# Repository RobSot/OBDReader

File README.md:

# OBDReader
OBD to USB interface development

The purpose of this development is to bring an open source OBD-USB interface to the comunity. Whith it you can develop your own applications above it. 
It has CAN connectivity via the OBD port and USB serial conectivity via the USB port.

*** The source code is organized like this:

1.- The folder src/Hardware_Source_code/ contains two folders. Both are MplabX 2.26 projects, one of them is the firmware and the other is the utility car emulator.
2.- The folder src/Software_Source_code/ contains one folder. This is the Qt creator 5 project and is the GUI application.
3.- In the src/ folder exist an .hex file containing the latest version of the OBDReader firmware ready to flash on the device.

Hope you enjoy it!!

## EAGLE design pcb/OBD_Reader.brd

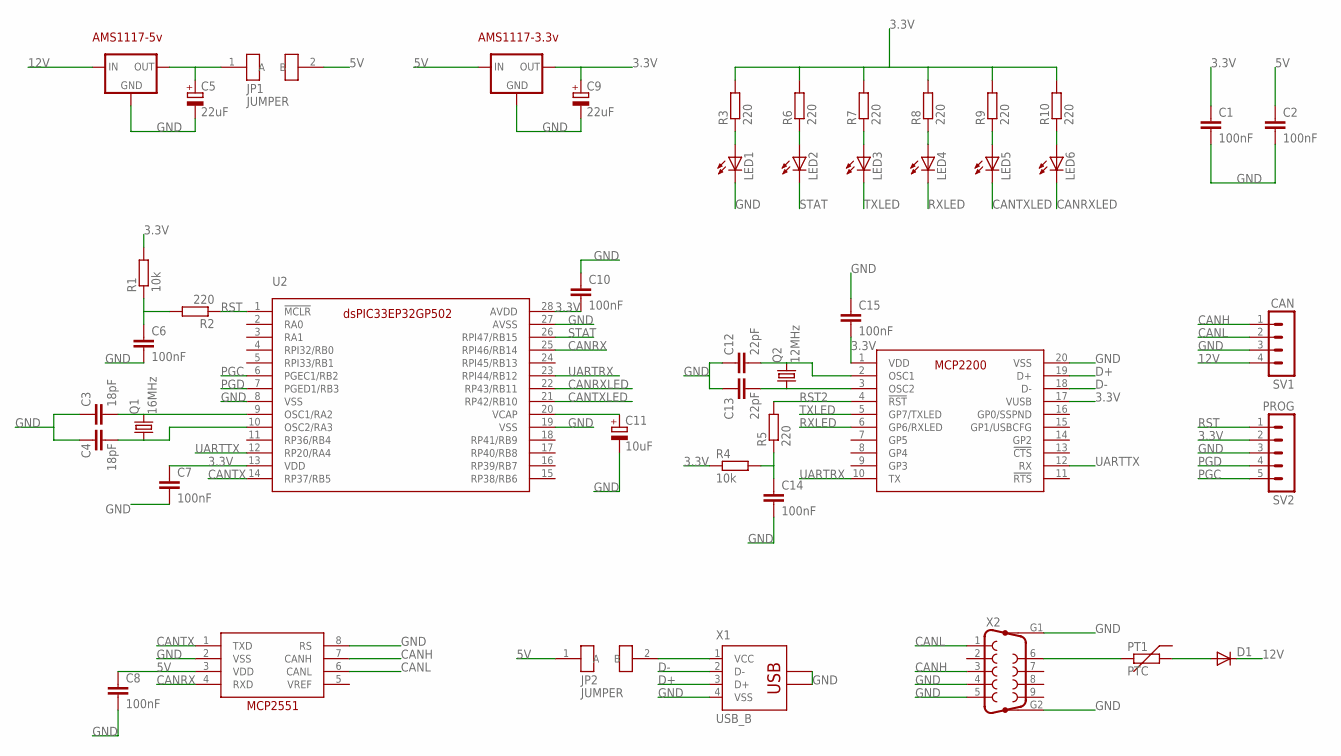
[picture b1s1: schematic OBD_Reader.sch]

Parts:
C1, C2, C6, C7, C8, C10, C14, C15: 100nF; C0603
C3, C4: 18pF; C0603
C5, C9: 22uF; CT3216
C11: 10uF; CT3216
C12, C13: 22pF; C0603
D1: DIODE-SMB; SMB
JP1, JP2: JUMPER; 1206
LED1, LED2, LED3, LED4, LED5, LED6: LEDCHIPLED_0603; CHIPLED_0603
PT1: PTC; PTC_1206
Q1: 16MHz; HC49/S
Q2: 12MHz; HC49/S
R1, R4: 10k; R0603
R2, R3, R5, R6, R7, R8, R9, R10: 220; R0603
SV1: CAN; MA04-1
SV2: PROG; MA05-1
U1: AMS1117_5V; SOT-223
U2: DSPIC33EP32GP502; SSOP28
U3: MCP2551; SOIC20
U4: AMS1117_3.3V; SOT-223
U5: MCP2200; SSOP20
X1: USB_B; 85-32004-00X
X2: F09HP

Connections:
3.3V: C1.1, C7.1, C9.+, C10.2, C15.2, R1.2, R3.2, R4.1, R6.2, R7.2, R8.2, R9.2, R10.2, SV2.2, U2.13 (VDD), U2.28 (AVDD), U4.2 (OUT), U5.1 (VDD), U5.17 (VUSB)
5V: C2.1, C8.1, JP1.2 (B), JP2.1 (A), U3.3 (VDD), U4.3 (IN)
12V: D1.C, SV1.4, U1.3 (IN)
CANH: SV1.1, U3.7 (CANH), X2.3
CANL: SV1.2, U3.6 (CANL), X2.1
CANRX: U2.25 (RPI46/RB14), U3.4 (RXD)
CANRXLED: LED6.C, U2.22 (RP43/RB11)
CANTX: U2.14 (RP37/RB5), U3.1 (TXD)
CANTXLED: LED5.C, U2.21 (RP42/RB10)
D+: U5.19 (D+), X1.3 (D+)
D-: U5.18 (D-), X1.2 (D-)
GND: C1.2, C2.2, C3.1, C4.1, C5.-, C6.2, C7.2, C8.2, C9.-, C10.1, C11.-, C12.1, C13.1, C14.2, C15.1, LED1.C, SV1.3, SV2.3, U1.1 (GND), U2.8 (VSS), U2.19 (VSS), U2.27 (AVSS), U3.2 (VSS), U3.8 (RS), U4.1 (GND), U5.20 (VSS), X1.4 (VSS), X1.M1 (C1), X1.M2 (C2), X2.4, X2.5, X2.G1, X2.G2
unnamed: C3.2, Q1.2, U2.9 (OSC1/RA2)
unnamed: C4.2, Q1.1, U2.10 (OSC2/RA3)
unnamed: C14.1, R4.2, R5.1
unnamed: C12.2, Q2.2, U5.2 (OSC1)
unnamed: C13.2, Q2.1, U5.3 (OSC2)
unnamed: C6.1, R1.1, R2.2
unnamed: JP2.2 (B), X1.1 (VCC)
unnamed: D1.A, PT1.2
unnamed: PT1.1, X2.6
unnamed: C5.+, JP1.1 (A), U1.2 (OUT)
unnamed: LED1.A, R3.1
unnamed: LED2.A, R6.1
unnamed: LED3.A, R7.1
unnamed: LED4.A, R8.1
unnamed: LED5.A, R9.1
unnamed: LED6.A, R10.1
unnamed: C11.+, U2.20 (VCAP)
PGC: SV2.5, U2.6 (PGEC1/RB2)
PGD: SV2.4, U2.7 (PGED1/RB3)
RST: R2.1, SV2.1, U2.1 (!MCLR)
RST2: R5.2, U5.4 (!RST)
RXLED: LED4.C, U5.6 (GP6/RXLED)
STAT: LED2.C, U2.26 (RPI47/RB15)
TXLED: LED3.C, U5.5 (GP7/TXLED)
UARTRX: U2.23 (RPI44/RB12), U5.10 (TX)
UARTTX: U2.12 (RP20/RA4), U5.12 (RX)

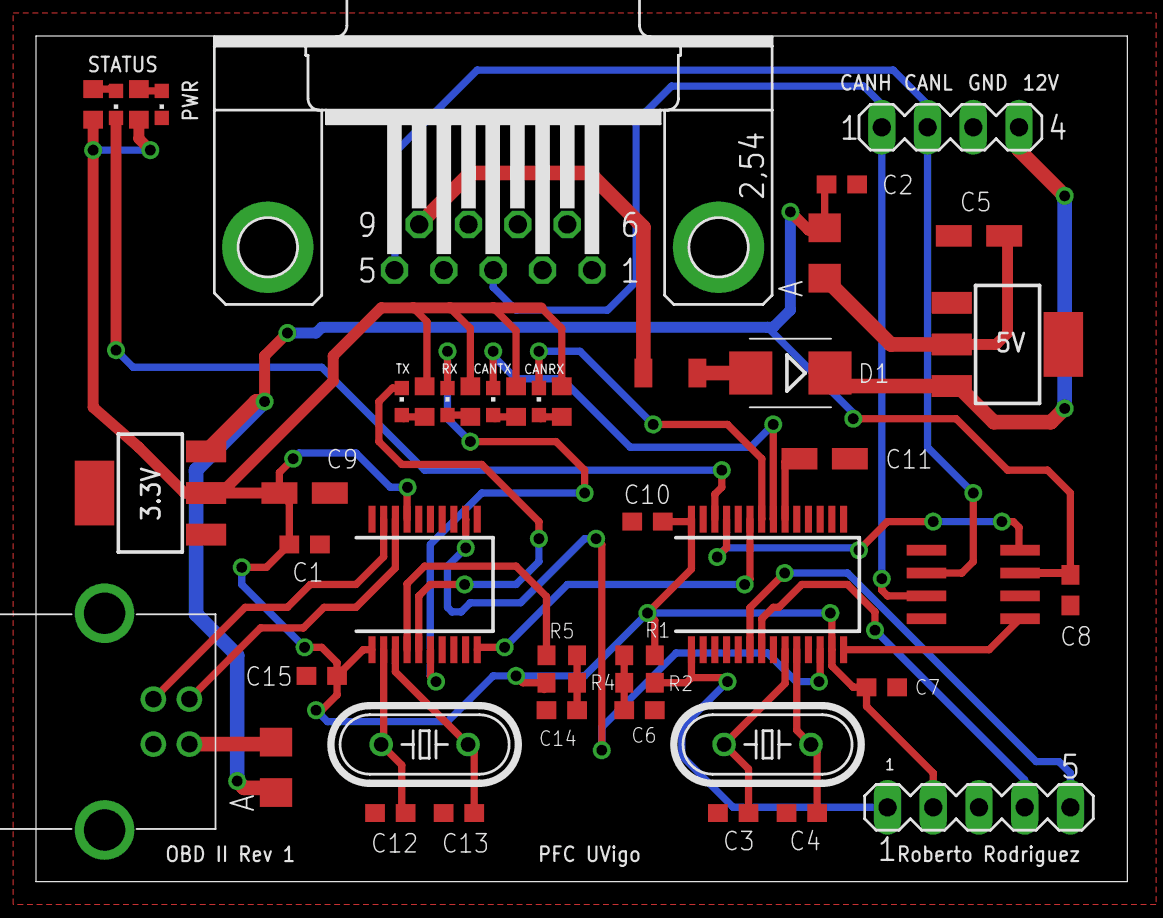
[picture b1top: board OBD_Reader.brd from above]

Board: 2 copper layers, 60.6 x 47.0 mm, 46 parts (0 on the bottom side), 38 nets.

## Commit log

2015-04-29 Initial commit. First stage of project
2015-08-18 Code refactor and organization. Added new versions
2015-08-29 Added PID selection window on GUI. Some bug fixes.
2015-09-26 Added latest versions and aplication installer
